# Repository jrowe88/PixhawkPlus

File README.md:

# Pixhawk Plus #
The [Pixhawk](https://pixhawk.org/choice) and [PX4](http://px4.io/) flight stack are workhorses in DIY drone world.  

Often paired with an OpenTX receiver such as the FrSky, you have a powerful combination.

Pixhawk Plus aims to make better use of this great combination by providing an easy-to-use, modular set of add-ons:

1. Telemetry pass-through from the Pixhawk to your OpenTX receiver.
2. Robust LED indicator lights--multiple arms, multiple programs.
3. Per-cell LIPO voltage monitoring.

## Getting Started ##
- Get the code
- Get the hardware
- Assemble and go!

[See the Wiki for complete instructions](http://#)

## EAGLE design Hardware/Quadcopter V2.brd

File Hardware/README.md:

# Pixhawk Plus Circuit Boards #
This folder contains Eagle files for corresponding hardware. These boards are not required, but make the packaging neater than soldering a bunch of wires to a Teensy 3.2.

You can order your own, simply wire to the Teensy, or come up with your own creation.  See the Wiki for more options and ideas.

##Primary Board:##
This code and "backpack" are designed to work with [Teensy 3.2](https://www.pjrc.com/store/teensy32.html) development board.  Probably would world with Feather, or Arduino Mini, but I haven't tried that.

##Quadcopter Backpack:##

- Order from [OSHPark.com](https://oshpark.com/shared_projects/TG4BuGQ4) or [contact me](mailto:jim.rowe@gmail.com) for spare boards I may be willing to send you for nominal fee.
- BOM Parts for the Backpack: [From DigiKey](http://www.digikey.com/short/tvfnt3)

##LED Leg:##

- Order from [OSHPark.com](https://oshpark.com/shared_projects/HVTKyU7v) or [contact me](mailto:jim.rowe@gmail.com) for spare boards I may be willing to send you for nominal fee.
- You can also use Adafruit NeoPixel or other strips of WS2812b RGB LED lights found from many distributors.

<a href="https://oshpark.com/shared_projects/HVTKyU7v"><br/></a>

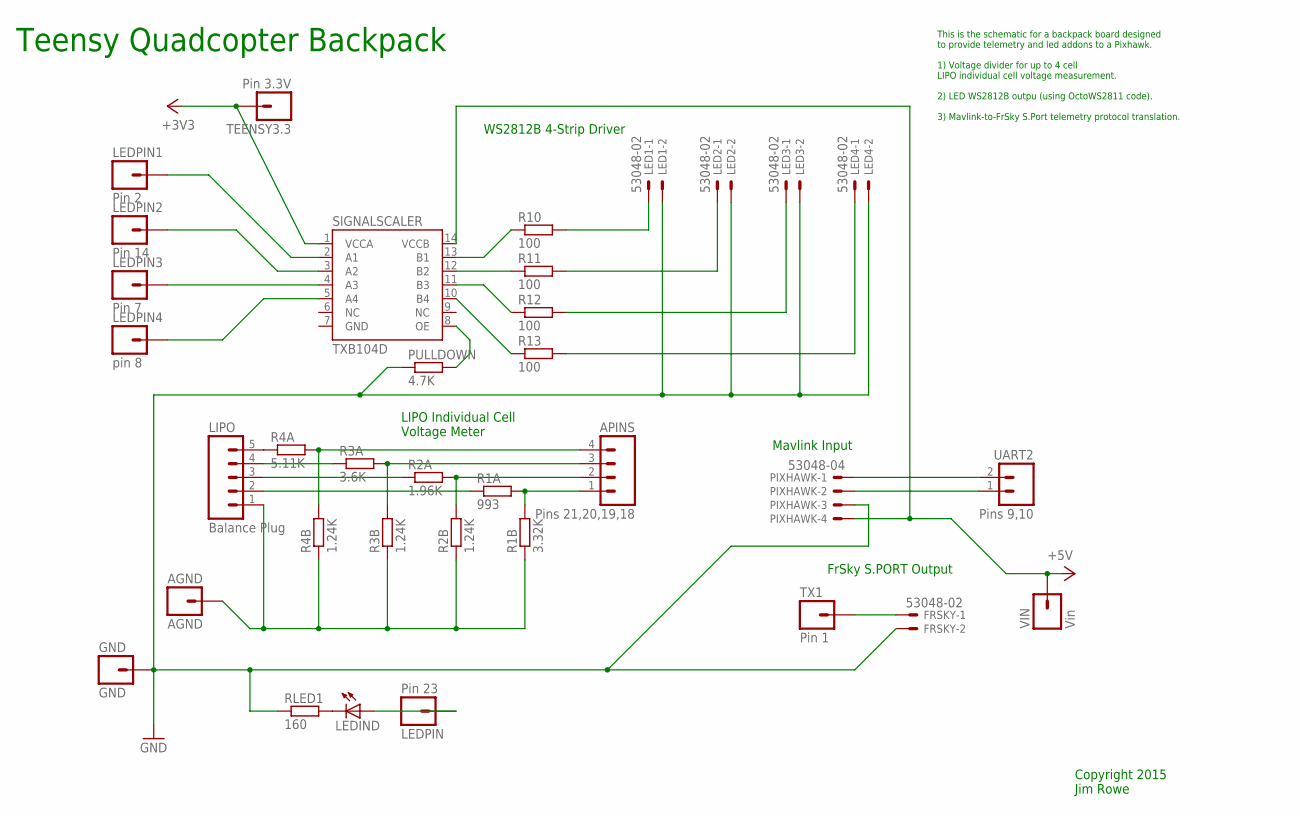
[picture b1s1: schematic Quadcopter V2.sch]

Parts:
AGND: AGND; 1X01_NO_SILK
APINS: Pins 21,20,19,18; 1X04_NO_SILK_ALL_ROUND
FRSKY: 53048-02
GND: GND; 1X01_NO_SILK
LED1, LED2, LED3, LED4: 53048-02
LEDIND: LEDCHIPLED_0603; CHIPLED_0603
LEDPIN: Pin 23; 1X01_NO_SILK
LEDPIN1: Pin 2; 1X01_NO_SILK
LEDPIN2: Pin 14; 1X01_NO_SILK
LEDPIN3: Pin 7; 1X01_NO_SILK
LEDPIN4: pin 8; 1X01_NO_SILK
LIPO: Balance Plug; 1X05_LOCK_LONGPADS
PIXHAWK: 53048-04
PULLDOWN: 4.7K; R0805
R1A: 993; R0805
R1B: 3.32K; R0805
R2A: 1.96K; R0805
R2B, R3B, R4B: 1.24K; R0805
R3A: 3.6K; R0805
R4A: 5.11K; R0805
R10, R11, R12, R13: 100; R0805
RLED1: 160; R0603
SIGNALSCALER: TXB104D; SOIC(D)-14
TEENSY3.3: Pin 3.3V; 1X01_NO_SILK
TX1: Pin 1; 1X01_NO_SILK
UART2: Pins 9,10; 1X02_NO_SILK
VIN: Vin; 1X01_NO_SILK

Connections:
+3V3: SIGNALSCALER.1 (VCCA), TEENSY3.3.1
+5V: PIXHAWK.4, SIGNALSCALER.14 (VCCB), VIN.1
GND: FRSKY.2, GND.1, LED1.2, LED2.2, LED3.2, LED4.2, PIXHAWK.3, PULLDOWN.1, RLED1.1, SIGNALSCALER.7 (GND)
unnamed: R10.1, SIGNALSCALER.13 (B1)
unnamed: R11.1, SIGNALSCALER.12 (B2)
unnamed: R12.1, SIGNALSCALER.11 (B3)
unnamed: R13.1, SIGNALSCALER.10 (B4)
unnamed: APINS.4, R4A.2, R4B.2
unnamed: APINS.3, R3A.2, R3B.2
unnamed: APINS.2, R2A.2, R2B.2
unnamed: LIPO.5, R4A.1
unnamed: LIPO.4, R3A.1
unnamed: LIPO.3, R2A.1
unnamed: LIPO.2, R1A.1
unnamed: LEDPIN1.1, SIGNALSCALER.2 (A1)
unnamed: LEDPIN2.1, SIGNALSCALER.3 (A2)
unnamed: LEDPIN3.1, SIGNALSCALER.4 (A3)
unnamed: LEDPIN4.1, SIGNALSCALER.5 (A4)
unnamed: AGND.1, LIPO.1, R1B.1, R2B.1, R3B.1, R4B.1
unnamed: APINS.1, R1A.2, R1B.2
unnamed: LED1.1, R10.2
unnamed: LED2.1, R11.2
unnamed: LED3.1, R12.2
unnamed: LED4.1, R13.2
unnamed: PIXHAWK.1, UART2.2
unnamed: PIXHAWK.2, UART2.1
unnamed: LEDIND.C, RLED1.2
unnamed: FRSKY.1, TX1.1
unnamed: PULLDOWN.2, SIGNALSCALER.8 (OE)
unnamed: LEDIND.A, LEDPIN.1

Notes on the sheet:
WS2812B 4-Strip Driver
Teensy Quadcopter Backpack
LIPO Individual Cell Voltage Meter
Mavlink Input
FrSky S.PORT Output
Copyright 2015 Jim Rowe
This is the schematic for a backpack board designed to provide telemetry and led addons to a Pixhawk. 1) Voltage divider for up to 4 cell LIPO individual cell voltage measurement. 2) LED WS2812B outpu (using OctoWS2811 code). 3) Mavlink-to-FrSky S.Port telemetry protocol translation.

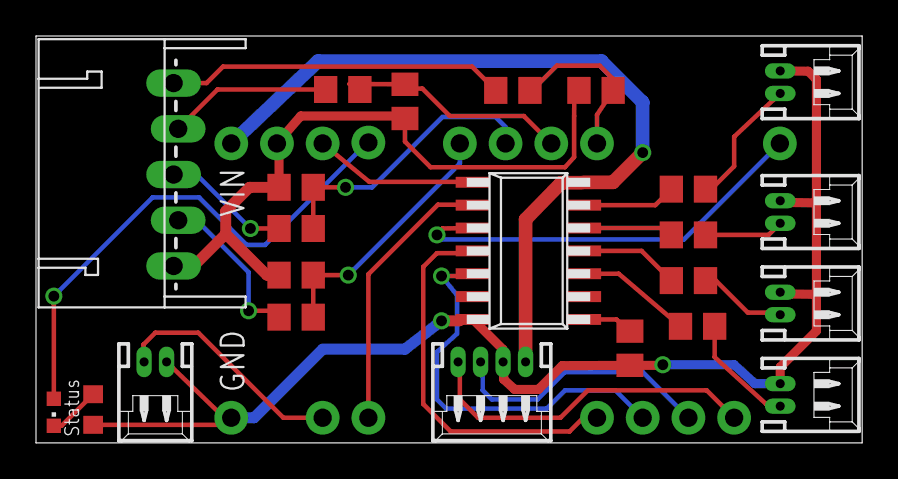
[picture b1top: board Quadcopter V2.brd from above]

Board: 2 copper layers, 45.9 x 22.6 mm, 35 parts (0 on the bottom side), 30 nets.

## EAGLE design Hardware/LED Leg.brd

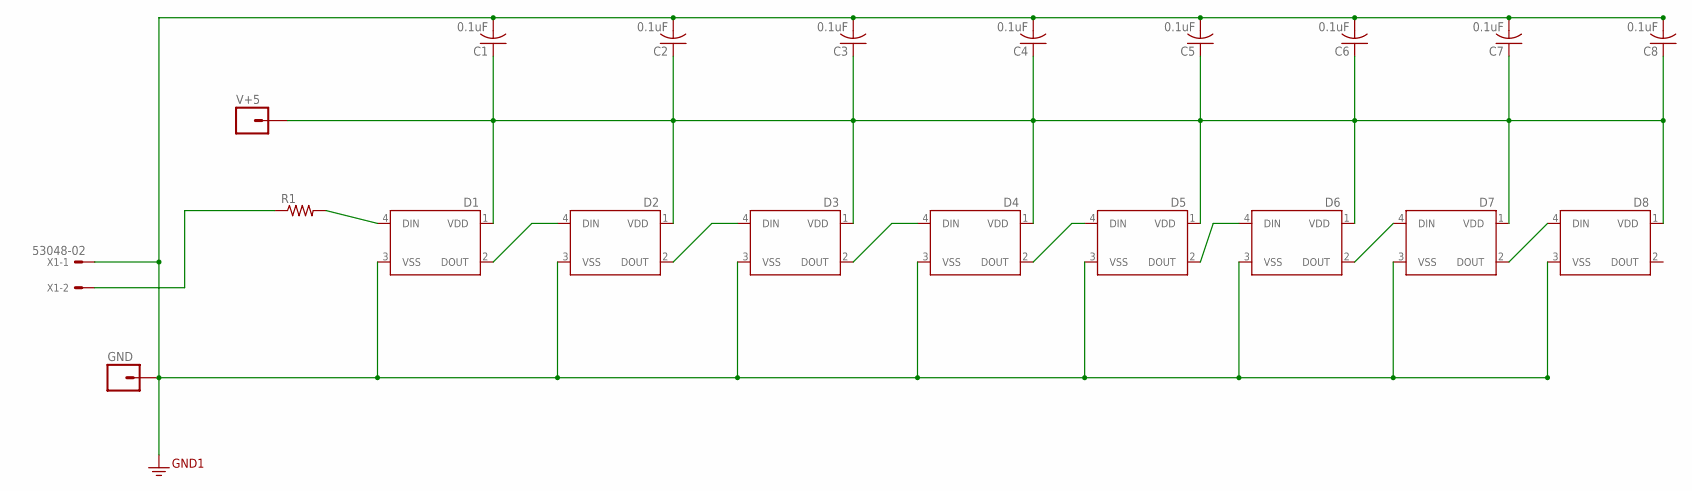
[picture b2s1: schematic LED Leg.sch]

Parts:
C1, C2, C3, C4, C5, C6, C7, C8: 0.1uF; C0603K
D1, D2, D3, D4, D5, D6, D7, D8: WS2812B
GND: M01NOSILK-KIT; 1X01NS-KIT
R1: R-US_R0603; R0603
V+5: M01NOSILK-KIT; 1X01NS-KIT
X1: 53048-02

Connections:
+5VOLTSUPPLY: C1.1, C2.1, C3.1, C4.1, C5.1, C6.1, C7.1, C8.1, D1.1 (VDD), D2.1 (VDD), D3.1 (VDD), D4.1 (VDD), D5.1 (VDD), D6.1 (VDD), D7.1 (VDD), D8.1 (VDD), V+5.1
GROUND: C1.2, C2.2, C3.2, C4.2, C5.2, C6.2, C7.2, C8.2, D1.3 (VSS), D2.3 (VSS), D3.3 (VSS), D4.3 (VSS), D5.3 (VSS), D6.3 (VSS), D7.3 (VSS), D8.3 (VSS), GND.1, X1.1
LEDSIGNAL: D1.4 (DIN), R1.2
LEDSIGNAL0: R1.1, X1.2
unnamed: D6.2 (DOUT), D7.4 (DIN)
unnamed: D7.2 (DOUT), D8.4 (DIN)
unnamed: D3.2 (DOUT), D4.4 (DIN)
unnamed: D4.2 (DOUT), D5.4 (DIN)
unnamed: D5.2 (DOUT), D6.4 (DIN)
SIGNAL: D1.2 (DOUT), D2.4 (DIN)
SIGNAL1: D2.2 (DOUT), D3.4 (DIN)

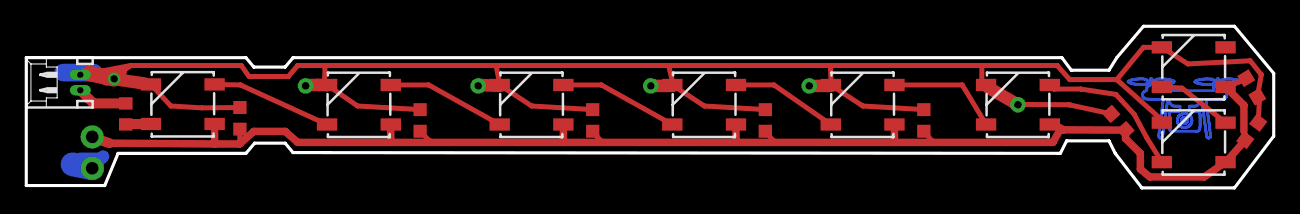
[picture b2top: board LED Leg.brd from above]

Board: 2 copper layers, 101.0 x 13.1 mm, 20 parts (0 on the bottom side), 11 nets.

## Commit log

2016-01-08 initial push
    initial push - beta version
2016-01-08 Added board files
2016-01-08 Added readme for hardware
2016-01-11 lipo monitor and smoothing updates
2016-01-11 license GNU to match mavlink_frskysport
2016-01-11 Adding library references and copies as of jan 1, 2016
2016-01-12 updates and reference information

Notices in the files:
Hardware/LED Leg.brd:
Big Daddy Drones (c)2015
parts and their libraries:
SparkFun-LED: Licensing: Creative Commons ShareAlike 4.0 International - https://creativecommons.org/licenses/by-sa/4.0
